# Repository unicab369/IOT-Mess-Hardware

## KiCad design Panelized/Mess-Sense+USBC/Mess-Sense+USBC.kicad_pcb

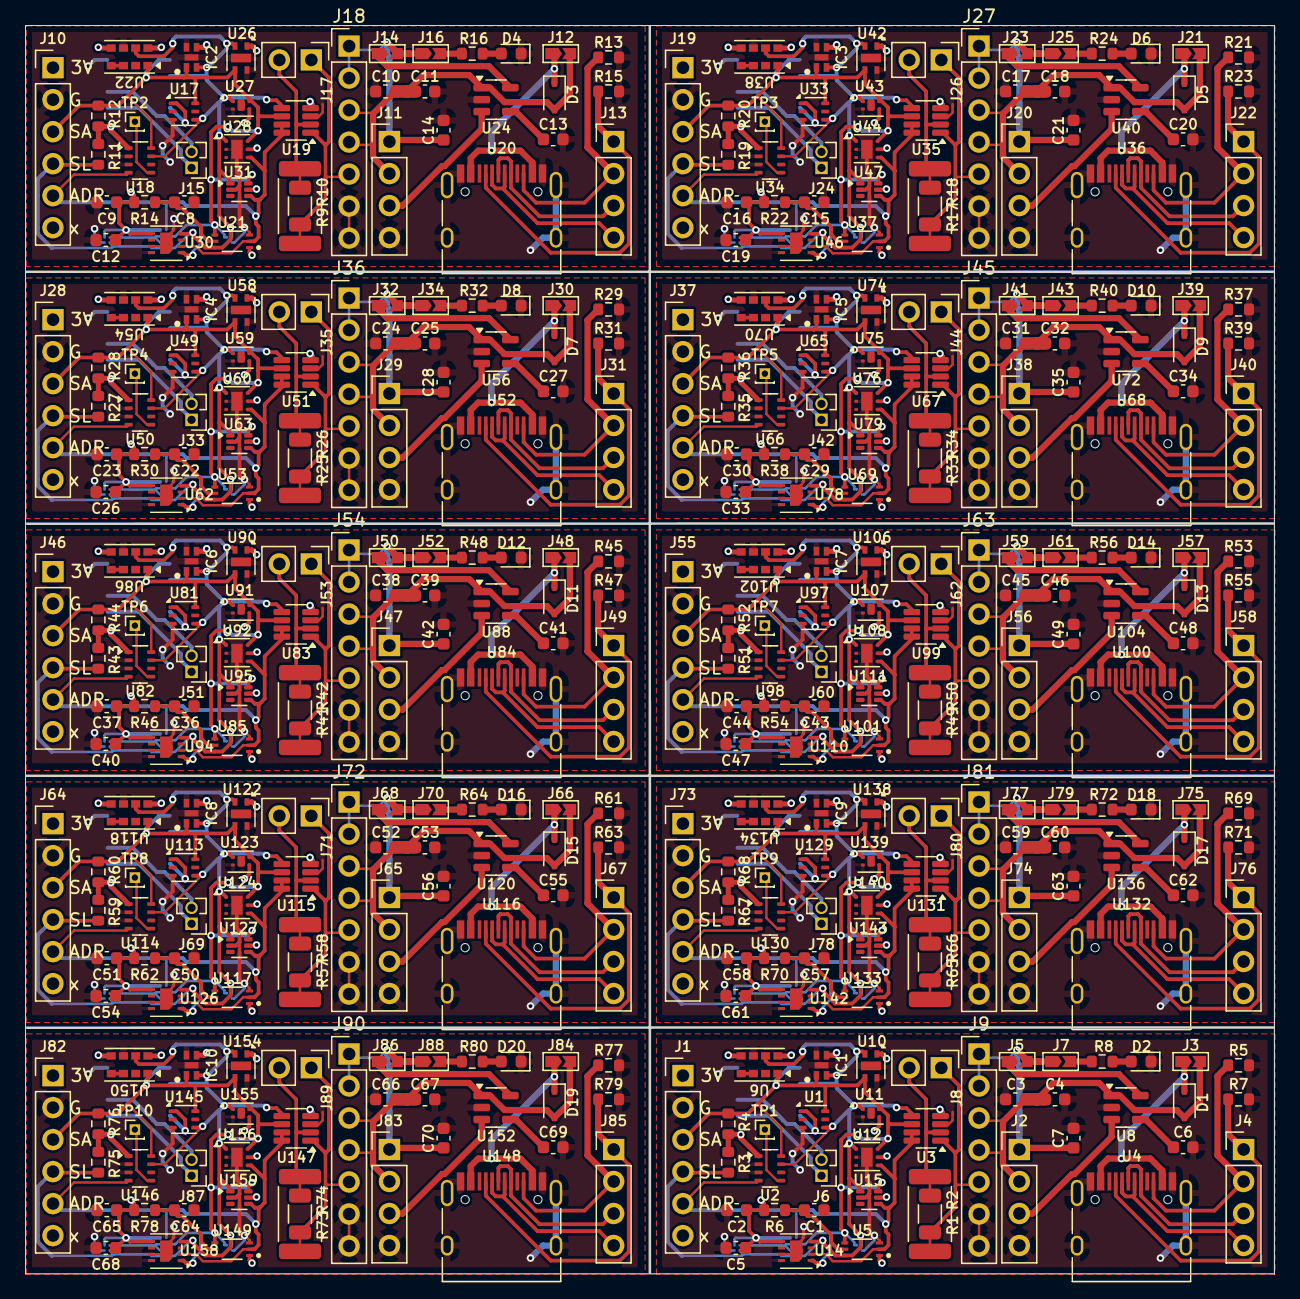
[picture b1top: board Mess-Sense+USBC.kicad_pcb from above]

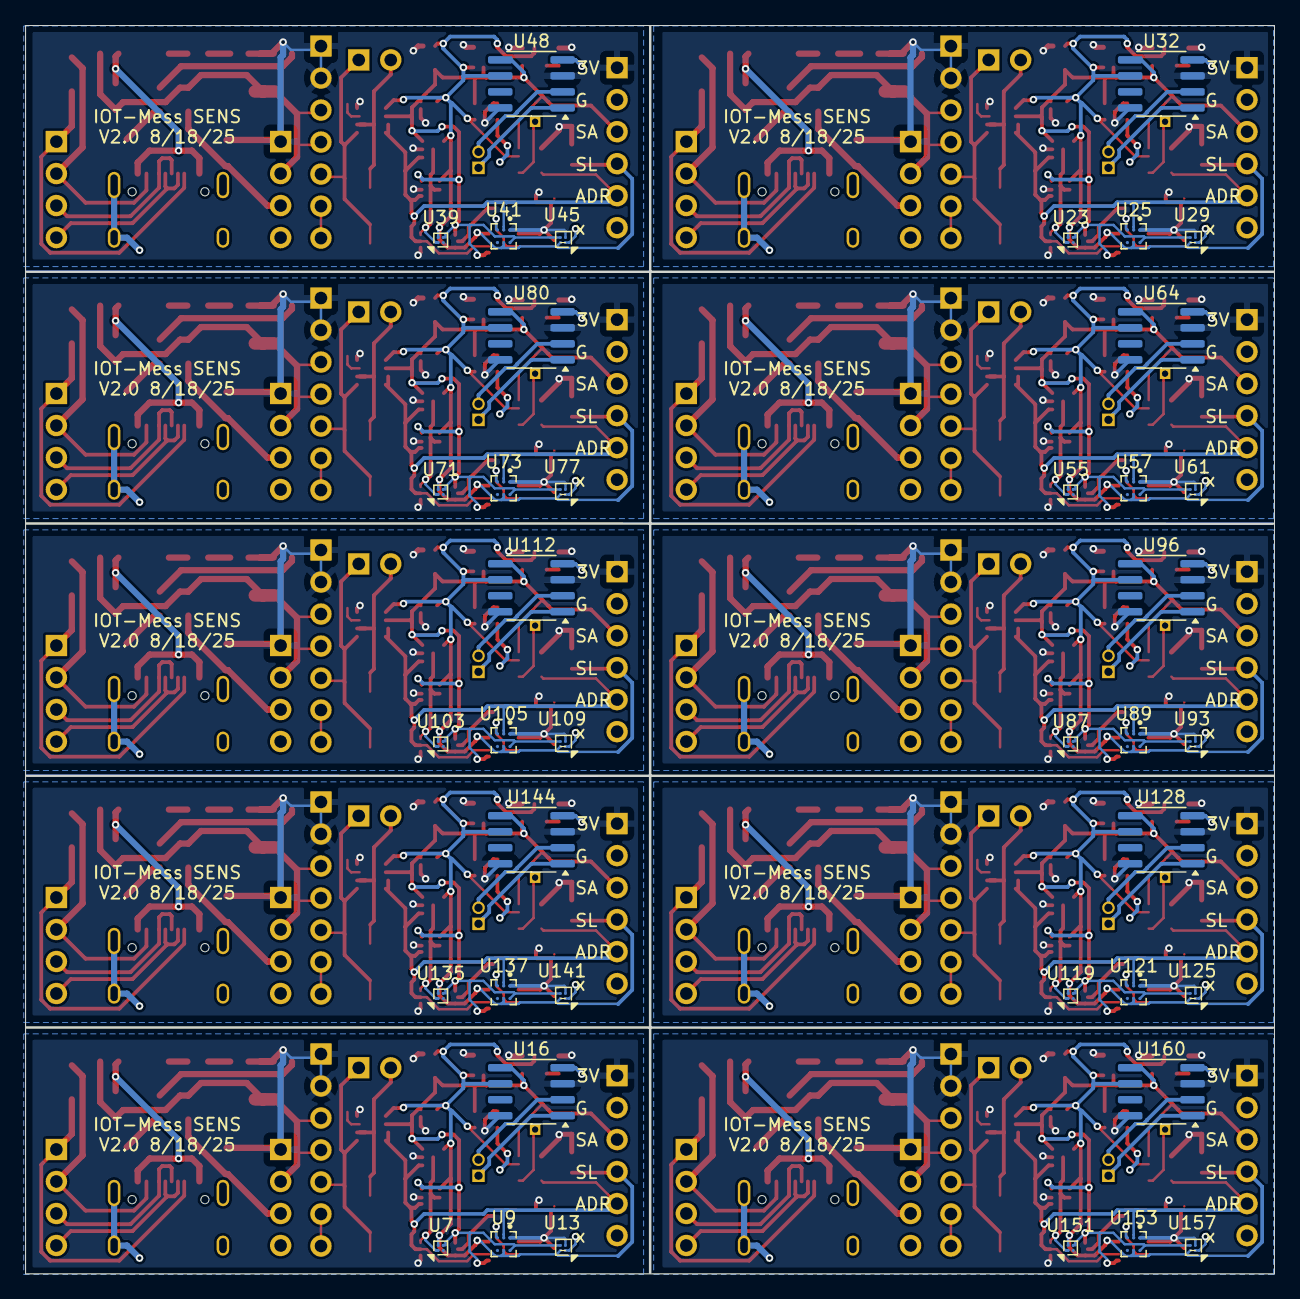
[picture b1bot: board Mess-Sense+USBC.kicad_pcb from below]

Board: 2 copper layers, 99.1 x 99.1 mm, 440 parts (40 on the bottom side), 23 nets.

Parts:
C1, C8, C15, C22, C29, C36, C43, C50, C57, C64: 0.1uF; C_0603_1608Metric
C2, C9, C16, C23, C30, C37, C44, C51, C58, C65: 1uF; C_0603_1608Metric
C3, C10, C17, C24, C31, C38, C45, C52, C59, C66: 10u; C_0603_1608Metric
C4, C7, C11, C14, C18, C21, C25, C28, C32, C35, C39, C42, C46, C49, C53, C56, C60, C63, C67, C70: 1u; C_0603_1608Metric
C5, C12, C19, C26, C33, C40, C47, C54, C61, C68: 2.2uF; C_0603_1608Metric
C6, C13, C20, C27, C34, C41, C48, C55, C62, C69: 22nF; C_0603_1608Metric
D1, D3, D5, D7, D9, D11, D13, D15, D17, D19: 1N5819WS; D_SOD-323
D2, D4, D6, D8, D10, D12, D14, D16, D18, D20: LED; LED_0603_1608Metric
IC1, IC2, IC3, IC4, IC5, IC6, IC7, IC8, IC9, IC10: SHT40I-AD1F-R2; SON80P150X150X59-5N
J1, J10, J19, J28, J37, J46, J55, J64, J73, J82: Conn_01x06_Pin; PinHeader_1x06_P2.54mm_Vertical
J2, J4, J11, J13, J20, J22, J29, J31, J38, J40, J47, J49, J56, J58, J65, J67, J74, J76, J83, J85: Conn_01x04_Pin; PinHeader_1x04_P2.54mm_Vertical
J3, J5, J7, J12, J14, J16, J21, J23, J25, J30, J32, J34, J39, J41, J43, J48, J50, J52, J57, J59, J61, J66, J68, J70, J75, J77, J79, J84, J86, J88: Jumper_2; Jumpper-triangle
J6, J15, J24, J33, J42, J51, J60, J69, J78, J87: Conn_01x02_Pin; PinHeader_1x02_P1.27mm_Vertical
J8, J17, J26, J35, J44, J53, J62, J71, J80, J89: Conn_01x02_Pin; PinHeader_1x02_P2.54mm_Vertical
J9, J18, J27, J36, J45, J54, J63, J72, J81, J90: Conn_01x07_Pin; PinHeader_1x07_P2.54mm_Vertical
R1, R9, R17, R25, R33, R41, R49, R57, R65, R73: 0.1; R_2512_6332Metric
R2, R10, R18, R26, R34, R42, R50, R58, R66, R74: 0.1; R_1206_3216Metric
R3, R4, R11, R12, R19, R20, R27, R28, R35, R36, R43, R44, R51, R52, R59, R60, R67, R68, R75, R76: 10K; R_0603_1608Metric
R5, R7, R13, R15, R21, R23, R29, R31, R37, R39, R45, R47, R53, R55, R61, R63, R69, R71, R77, R79: 5.1K; R_0603_1608Metric
R6, R14, R22, R30, R38, R46, R54, R62, R70, R78: 5K; R_0603_1608Metric
R8, R16, R24, R32, R40, R48, R56, R64, R72, R80: R; R_0603_1608Metric
TP1, TP2, TP3, TP4, TP5, TP6, TP7, TP8, TP9, TP10: TestPoint; PinHeader_1x01_P1.00mm_Vertical
U1, U17, U33, U49, U65, U81, U97, U113, U129, U145: LTR-303/308; Lite-On_LTR-303ALS-01
U2, U18, U34, U50, U66, U82, U98, U114, U130, U146: LTR-507ALS
U3, U19, U35, U51, U67, U83, U99, U115, U131, U147: INA219AxDCN; SOT-23-8
U4, U20, U36, U52, U68, U84, U100, U116, U132, U148: USB_C_Receptacle_USB2.0_16P; USB_C_Receptacle_HRO_TYPE-C-31-M-12
U5, U21, U37, U53, U69, U85, U101, U117, U133, U149: BH1750FVI-TR; XDCR_BH1750FVI-TR
U6, U22, U38, U54, U70, U86, U102, U118, U134, U150: APDS-9960; Avago_APDS-9960
U7, U23, U39, U55, U71, U87, U103, U119, U135, U151: MMC5633NJL/WLP-4; WLP-4_0.86x0.86mm_P0.4mm
U8, U24, U40, U56, U72, U88, U104, U120, U136, U152: ME6211C33M5; SOT-23-5
U9, U25, U41, U57, U73, U89, U105, U121, U137, U153: HDC2010/DSBGA-6; BGA6C100X50P2X3_HDC2010YPAR
U10, U26, U42, U58, U74, U90, U106, U122, U138, U154: ENS210; AMS_QFN-4-1EP_2x2mm_P0.95mm_EP0.7x1.6mm
U11, U27, U43, U59, U75, U91, U107, U123, U139, U155: MTS4 0.1C DFN-4L; DFN-4L
U12, U28, U44, U60, U76, U92, U108, U124, U140, U156: T117W 0.1C DFN-6L; DFN-6L
U13, U29, U45, U61, U77, U93, U109, U125, U141, U157: QMC6309/WLCSP-4; WLCSP-4_0.8x0.8mm_Layout2x2_P0.4mm
U14, U30, U46, U62, U78, U94, U110, U126, U142, U158: SHT31-DIS; Sensirion_DFN-8-1EP_2.5x2.5mm_P0.5mm_EP1.1x1.7mm
U15, U31, U47, U63, U79, U95, U111, U127, U143, U159: TMP102xxDRL 0.5C SOT-563; SOT-563
U16, U32, U48, U64, U80, U96, U112, U128, U144, U160: DS1307Z+; SOIC-8_3.9x4.9mm_P1.27mm

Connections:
5V: C3.1, C4.1, C10.1, C11.1, C17.1, C18.1, C24.1, C25.1, C31.1, C32.1, C38.1, C39.1, C45.1, C46.1, C52.1, C53.1, C59.1, C60.1, C66.1, C67.1, D1.2 (A), D3.2 (A), D5.2 (A), D7.2 (A), D9.2 (A), D11.2 (A), D13.2 (A), D15.2 (A), D17.2 (A), D19.2 (A), J2.2, J3.2 (B), J9.3, J9.4, J11.2, J12.2 (B), J18.3, J18.4, J20.2, J21.2 (B), J27.3, J27.4, J29.2, J30.2 (B), J36.3, J36.4, J38.2, J39.2 (B), J45.3, J45.4, J47.2, J48.2 (B), J54.3, J54.4, J56.2, J57.2 (B), J63.3, J63.4, J65.2, J66.2 (B), J72.3, J72.4, J74.2, J75.2 (B), J81.3, J81.4, J83.2, J84.2 (B), J90.3, J90.4, U8.1 (V_{IN}), U24.1 (V_{IN}), U40.1 (V_{IN}), U56.1 (V_{IN}), U72.1 (V_{IN}), U88.1 (V_{IN}), U104.1 (V_{IN}), U120.1 (V_{IN}), U136.1 (V_{IN}), U152.1 (V_{IN})
+3.3V: C2.1, C5.1, C7.1, C9.1, C12.1, C14.1, C16.1, C19.1, C21.1, C23.1, C26.1, C28.1, C30.1, C33.1, C35.1, C37.1, C40.1, C42.1, C44.1, C47.1, C49.1, C51.1, C54.1, C56.1, C58.1, C61.1, C63.1, C65.1, C68.1, C70.1, IC1.3 (VDD), IC2.3 (VDD), IC3.3 (VDD), IC4.3 (VDD), IC5.3 (VDD), IC6.3 (VDD), IC7.3 (VDD), IC8.3 (VDD), IC9.3 (VDD), IC10.3 (VDD), J1.1, J2.1, J5.2 (B), J7.1 (A), J9.1, J9.2, J10.1, J11.1, J14.2 (B), J16.1 (A), J18.1, J18.2, J19.1, J20.1, J23.2 (B), J25.1 (A), J27.1, J27.2, J28.1, J29.1, J32.2 (B), J34.1 (A), J36.1, J36.2, J37.1, J38.1, J41.2 (B), J43.1 (A), J45.1, J45.2, J46.1, J47.1, J50.2 (B), J52.1 (A), J54.1, J54.2, J55.1, J56.1, J59.2 (B), J61.1 (A), J63.1, J63.2, J64.1, J65.1, J68.2 (B), J70.1 (A), J72.1, J72.2, J73.1, J74.1, J77.2 (B), J79.1 (A), J81.1, J81.2, J82.1, J83.1, J86.2 (B), J88.1 (A), J90.1, J90.2, R3.2, R4.1, R6.1, R11.2, R12.1, R14.1, R19.2, R20.1, R22.1, R27.2, R28.1, R30.1, R35.2, R36.1, R38.1, R43.2, R44.1, R46.1, R51.2, R52.1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
ADDR: J1.5, J10.5, J19.5, J28.5, J37.5, J46.5, J55.5, J64.5, J73.5, J82.5, U2.4 (ADDR), U3.7 (A0), U3.8 (A1), U5.2 (ADDR), U9.B1 (ADDR), U12.4 (ADDR), U14.2 (ADDR), U15.4 (ADD0), U18.4 (ADDR), U19.7 (A0), U19.8 (A1), U21.2 (ADDR), U25.B1 (ADDR), U28.4 (ADDR), U30.2 (ADDR), U31.4 (ADD0), U34.4 (ADDR), U35.7 (A0), U35.8 (A1), U37.2 (ADDR), U41.B1 (ADDR), U44.4 (ADDR), U46.2 (ADDR), U47.4 (ADD0), U50.4 (ADDR), U51.7 (A0), U51.8 (A1), U53.2 (ADDR), U57.B1 (ADDR), U60.4 (ADDR), U62.2 (ADDR), U63.4 (ADD0), U66.4 (ADDR), U67.7 (A0), U67.8 (A1), U69.2 (ADDR), U73.B1 (ADDR), U76.4 (ADDR), U78.2 (ADDR), U79.4 (ADD0), U82.4 (ADDR), U83.7 (A0), U83.8 (A1), U85.2 (ADDR), U89.B1 (ADDR), U92.4 (ADDR), U94.2 (ADDR), U95.4 (ADD0), U98.4 (ADDR), U99.7 (A0), U99.8 (A1), U101.2 (ADDR), U105.B1 (ADDR), U108.4 (ADDR), U110.2 (ADDR), U111.4 (ADD0), U114.4 (ADDR), U115.7 (A0), U115.8 (A1), U117.2 (ADDR), U121.B1 (ADDR), U124.4 (ADDR), U126.2 (ADDR), U127.4 (ADD0), U130.4 (ADDR), U131.7 (A0), U131.8 (A1), U133.2 (ADDR), U137.B1 (ADDR), U140.4 (ADDR), U142.2 (ADDR), U143.4 (ADD0), U146.4 (ADDR), U147.7 (A0), U147.8 (A1), U149.2 (ADDR), U153.B1 (ADDR), U156.4 (ADDR), U158.2 (ADDR), U159.4 (ADD0)
CC1: J4.1, J13.1, J22.1, J31.1, J40.1, J49.1, J58.1, J67.1, J76.1, J85.1, R7.1, R15.1, R23.1, R31.1, R39.1, R47.1, R55.1, R63.1, R71.1, R79.1, U4.A5 (CC1), U20.A5 (CC1), U36.A5 (CC1), U52.A5 (CC1), U68.A5 (CC1), U84.A5 (CC1), U100.A5 (CC1), U116.A5 (CC1), U132.A5 (CC1), U148.A5 (CC1)
CC2: J4.2, J13.2, J22.2, J31.2, J40.2, J49.2, J58.2, J67.2, J76.2, J85.2, R5.1, R13.1, R21.1, R29.1, R37.1, R45.1, R53.1, R61.1, R69.1, R77.1, U4.B5 (CC2), U20.B5 (CC2), U36.B5 (CC2), U52.B5 (CC2), U68.B5 (CC2), U84.B5 (CC2), U100.B5 (CC2), U116.B5 (CC2), U132.B5 (CC2), U148.B5 (CC2)
CE: J2.3, J11.3, J20.3, J29.3, J38.3, J47.3, J56.3, J65.3, J74.3, J83.3, U8.3 (CE), U24.3 (CE), U40.3 (CE), U56.3 (CE), U72.3 (CE), U88.3 (CE), U104.3 (CE), U120.3 (CE), U136.3 (CE), U152.3 (CE)
D+: J4.3, J13.3, J22.3, J31.3, J40.3, J49.3, J58.3, J67.3, J76.3, J85.3, U4.A6 (D+), U4.B6 (D+), U20.A6 (D+), U20.B6 (D+), U36.A6 (D+), U36.B6 (D+), U52.A6 (D+), U52.B6 (D+), U68.A6 (D+), U68.B6 (D+), U84.A6 (D+), U84.B6 (D+), U100.A6 (D+), U100.B6 (D+), U116.A6 (D+), U116.B6 (D+), U132.A6 (D+), U132.B6 (D+), U148.A6 (D+), U148.B6 (D+)
D-: J4.4, J13.4, J22.4, J31.4, J40.4, J49.4, J58.4, J67.4, J76.4, J85.4, U4.A7 (D-), U4.B7 (D-), U20.A7 (D-), U20.B7 (D-), U36.A7 (D-), U36.B7 (D-), U52.A7 (D-), U52.B7 (D-), U68.A7 (D-), U68.B7 (D-), U84.A7 (D-), U84.B7 (D-), U100.A7 (D-), U100.B7 (D-), U116.A7 (D-), U116.B7 (D-), U132.A7 (D-), U132.B7 (D-), U148.A7 (D-), U148.B7 (D-)
GND: C1.2, C2.2, C3.2, C4.2, C5.2, C6.2, C7.2, C8.2, C9.2, C10.2, C11.2, C12.2, C13.2, C14.2, C15.2, C16.2, C17.2, C18.2, C19.2, C20.2, C21.2, C22.2, C23.2, C24.2, C25.2, C26.2, C27.2, C28.2, C29.2, C30.2, C31.2, C32.2, C33.2, C34.2, C35.2, C36.2, C37.2, C38.2, C39.2, C40.2, C41.2, C42.2, C43.2, C44.2, C45.2, C46.2, C47.2, C48.2, C49.2, C50.2, C51.2, C52.2, C53.2, C54.2, C55.2, C56.2, C57.2, C58.2, C59.2, C60.2, C61.2, C62.2, C63.2, C64.2, C65.2, C66.2, C67.2, C68.2, C69.2, C70.2, D2.1 (K), D4.1 (K), D6.1 (K), D8.1 (K), D10.1 (K), D12.1 (K), D14.1 (K), D16.1 (K), D18.1 (K), D20.1 (K), IC1.4 (VSS), IC1.5 (EP), IC2.4 (VSS), IC2.5 (EP), IC3.4 (VSS), IC3.5 (EP), IC4.4 (VSS), IC4.5 (EP), IC5.4 (VSS), IC5.5 (EP), IC6.4 (VSS), IC6.5 (EP), IC7.4 (VSS), IC7.5 (EP), IC8.4 (VSS), IC8.5 (EP), IC9.4 (VSS), IC9.5 (EP), IC10.4 (VSS), IC10.5 (EP), J1.2, J2.4, J9.6, J9.7, J10.2, J11.4, J18.6, J18.7, J19.2, J20.4, J27.6, J27.7, J28.2, J29.4, J36.6, J36.7, J37.2, J38.4, J45.6, J45.7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
unnamed: D1.1 (K), D3.1 (K), D5.1 (K), D7.1 (K), D9.1 (K), D11.1 (K), D13.1 (K), D15.1 (K), D17.1 (K), D19.1 (K), J3.1 (A), J12.1 (A), J21.1 (A), J30.1 (A), J39.1 (A), J48.1 (A), J57.1 (A), J66.1 (A), J75.1 (A), J84.1 (A), U4.A4 (VBUS), U4.A9 (VBUS), U4.B4 (VBUS), U4.B9 (VBUS), U20.A4 (VBUS), U20.A9 (VBUS), U20.B4 (VBUS), U20.B9 (VBUS), U36.A4 (VBUS), U36.A9 (VBUS), U36.B4 (VBUS), U36.B9 (VBUS), U52.A4 (VBUS), U52.A9 (VBUS), U52.B4 (VBUS), U52.B9 (VBUS), U68.A4 (VBUS), U68.A9 (VBUS), U68.B4 (VBUS), U68.B9 (VBUS), U84.A4 (VBUS), U84.A9 (VBUS), U84.B4 (VBUS), U84.B9 (VBUS), U100.A4 (VBUS), U100.A9 (VBUS), U100.B4 (VBUS), U100.B9 (VBUS), U116.A4 (VBUS), U116.A9 (VBUS), U116.B4 (VBUS), U116.B9 (VBUS), U132.A4 (VBUS), U132.A9 (VBUS), U132.B4 (VBUS), U132.B9 (VBUS), U148.A4 (VBUS), U148.A9 (VBUS), U148.B4 (VBUS), U148.B9 (VBUS)
unnamed: D2.2 (A), D4.2 (A), D6.2 (A), D8.2 (A), D10.2 (A), D12.2 (A), D14.2 (A), D16.2 (A), D18.2 (A), D20.2 (A), R8.1, R16.1, R24.1, R32.1, R40.1, R48.1, R56.1, R64.1, R72.1, R80.1
unnamed: J5.1 (A), J14.1 (A), J23.1 (A), J32.1 (A), J41.1 (A), J50.1 (A), J59.1 (A), J68.1 (A), J77.1 (A), J86.1 (A), U8.5 (V_{OUT}), U24.5 (V_{OUT}), U40.5 (V_{OUT}), U56.5 (V_{OUT}), U72.5 (V_{OUT}), U88.5 (V_{OUT}), U104.5 (V_{OUT}), U120.5 (V_{OUT}), U136.5 (V_{OUT}), U152.5 (V_{OUT})
unnamed: J6.1, J15.1, J24.1, J33.1, J42.1, J51.1, J60.1, J69.1, J78.1, J87.1, U16.1 (X1), U32.1 (X1), U48.1 (X1), U64.1 (X1), U80.1 (X1), U96.1 (X1), U112.1 (X1), U128.1 (X1), U144.1 (X1), U160.1 (X1)
unnamed: J6.2, J15.2, J24.2, J33.2, J42.2, J51.2, J60.2, J69.2, J78.2, J87.2, U16.2 (X2), U32.2 (X2), U48.2 (X2), U64.2 (X2), U80.2 (X2), U96.2 (X2), U112.2 (X2), U128.2 (X2), U144.2 (X2), U160.2 (X2)
unnamed: J7.2 (B), J16.2 (B), J25.2 (B), J34.2 (B), J43.2 (B), J52.2 (B), J61.2 (B), J70.2 (B), J79.2 (B), J88.2 (B), R8.2, R16.2, R24.2, R32.2, R40.2, R48.2, R56.2, R64.2, R72.2, R80.2
unnamed: J8.1, J9.5, J17.1, J18.5, J26.1, J27.5, J35.1, J36.5, J44.1, J45.5, J53.1, J54.5, J62.1, J63.5, J71.1, J72.5, J80.1, J81.5, J89.1, J90.5, R1.1, R2.1, R9.1, R10.1, R17.1, R18.1, R25.1, R26.1, R33.1, R34.1, R41.1, R42.1, R49.1, R50.1, R57.1, R58.1, R65.1, R66.1, R73.1, R74.1, U3.1 (IN+), U19.1 (IN+), U35.1 (IN+), U51.1 (IN+), U67.1 (IN+), U83.1 (IN+), U99.1 (IN+), U115.1 (IN+), U131.1 (IN+), U147.1 (IN+)
unnamed: J8.2, J17.2, J26.2, J35.2, J44.2, J53.2, J62.2, J71.2, J80.2, J89.2, R1.2, R2.2, R9.2, R10.2, R17.2, R18.2, R25.2, R26.2, R33.2, R34.2, R41.2, R42.2, R49.2, R50.2, R57.2, R58.2, R65.2, R66.2, R73.2, R74.2, U3.2 (IN-), U19.2 (IN-), U35.2 (IN-), U51.2 (IN-), U67.2 (IN-), U83.2 (IN-), U99.2 (IN-), U115.2 (IN-), U131.2 (IN-), U147.2 (IN-)
unnamed: TP1.1, TP2.1, TP3.1, TP4.1, TP5.1, TP6.1, TP7.1, TP8.1, TP9.1, TP10.1, U2.5 (VLED), U18.5 (VLED), U34.5 (VLED), U50.5 (VLED), U66.5 (VLED), U82.5 (VLED), U98.5 (VLED), U114.5 (VLED), U130.5 (VLED), U146.5 (VLED)
unnamed: C1.1, C8.1, C15.1, C22.1, C29.1, C36.1, C43.1, C50.1, C57.1, C64.1, R6.2, R14.2, R22.2, R30.2, R38.2, R46.2, R54.2, R62.2, R70.2, R78.2, U5.5 (DVI), U21.5 (DVI), U37.5 (DVI), U53.5 (DVI), U69.5 (DVI), U85.5 (DVI), U101.5 (DVI), U117.5 (DVI), U133.5 (DVI), U149.5 (DVI)
unnamed: U6.3 (LDR), U6.4 (LED_K), U22.3 (LDR), U22.4 (LED_K), U38.3 (LDR), U38.4 (LED_K), U54.3 (LDR), U54.4 (LED_K), U70.3 (LDR), U70.4 (LED_K), U86.3 (LDR), U86.4 (LED_K), U102.3 (LDR), U102.4 (LED_K), U118.3 (LDR), U118.4 (LED_K), U134.3 (LDR), U134.4 (LED_K), U150.3 (LDR), U150.4 (LED_K)
unnamed: C6.1, C13.1, C20.1, C27.1, C34.1, C41.1, C48.1, C55.1, C62.1, C69.1, U8.4 (NC), U24.4 (NC), U40.4 (NC), U56.4 (NC), U72.4 (NC), U88.4 (NC), U104.4 (NC), U120.4 (NC), U136.4 (NC), U152.4 (NC)
SCL_0: IC1.2 (SCL), IC2.2 (SCL), IC3.2 (SCL), IC4.2 (SCL), IC5.2 (SCL), IC6.2 (SCL), IC7.2 (SCL), IC8.2 (SCL), IC9.2 (SCL), IC10.2 (SCL), J1.4, J10.4, J19.4, J28.4, J37.4, J46.4, J55.4, J64.4, J73.4, J82.4, R3.1, R11.1, R19.1, R27.1, R35.1, R43.1, R51.1, R59.1, R67.1, R75.1, U1.4 (SCL), U2.7 (SCL), U3.5 (SCL), U5.6 (SCL), U6.7 (SCL), U7.A2 (SCL), U9.B2 (SCL), U10.2 (SCL), U11.1 (SCL), U12.1 (SCL), U13.A2 (SCL), U14.4 (SCL), U15.1 (SCL), U16.6 (SCL), U17.4 (SCL), U18.7 (SCL), U19.5 (SCL), U21.6 (SCL), U22.7 (SCL), U23.A2 (SCL), U25.B2 (SCL), U26.2 (SCL), U27.1 (SCL), U28.1 (SCL), U29.A2 (SCL), U30.4 (SCL), U31.1 (SCL), U32.6 (SCL), U33.4 (SCL), U34.7 (SCL), U35.5 (SCL), U37.6 (SCL), U38.7 (SCL), U39.A2 (SCL), U41.B2 (SCL), U42.2 (SCL), U43.1 (SCL), U44.1 (SCL), U45.A2 (SCL), U46.4 (SCL), U47.1 (SCL), U48.6 (SCL), U49.4 (SCL), U50.7 (SCL), U51.5 (SCL), U53.6 (SCL), U54.7 (SCL), U55.A2 (SCL), U57.B2 (SCL), U58.2 (SCL), U59.1 (SCL), U60.1 (SCL), U61.A2 (SCL), U62.4 (SCL), U63.1 (SCL), U64.6 (SCL), U65.4 (SCL), U66.7 (SCL), U67.5 (SCL), U69.6 (SCL), U70.7 (SCL), U71.A2 (SCL), U73.B2 (SCL), U74.2 (SCL), U75.1 (SCL), U76.1 (SCL), U77.A2 (SCL), U78.4 (SCL), U79.1 (SCL), U80.6 (SCL), U81.4 (SCL), U82.7 (SCL), U83.5 (SCL), U85.6 (SCL), U86.7 (SCL), U87.A2 (SCL), U89.B2 (SCL), U90.2 (SCL), U91.1 (SCL), U92.1 (SCL), U93.A2 (SCL), U94.4 (SCL), U95.1 (SCL), U96.6 (SCL), U97.4 (SCL), U98.7 (SCL), U99.5 (SCL), U101.6 (SCL), U102.7 (SCL), U103.A2 (SCL)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
SDA_0: IC1.1 (SDA), IC2.1 (SDA), IC3.1 (SDA), IC4.1 (SDA), IC5.1 (SDA), IC6.1 (SDA), IC7.1 (SDA), IC8.1 (SDA), IC9.1 (SDA), IC10.1 (SDA), J1.3, J10.3, J19.3, J28.3, J37.3, J46.3, J55.3, J64.3, J73.3, J82.3, R4.2, R12.2, R20.2, R28.2, R36.2, R44.2, R52.2, R60.2, R68.2, R76.2, U1.6 (SDA), U2.8 (SDA), U3.6 (SDA), U5.4 (SDA), U6.1 (SDA), U7.B2 (SDA), U9.A2 (SDA), U10.3 (SDA), U11.4 (SDA), U12.6 (SDA), U13.B2 (SDA), U14.1 (SDA), U15.6 (SDA), U16.5 (SDA), U17.6 (SDA), U18.8 (SDA), U19.6 (SDA), U21.4 (SDA), U22.1 (SDA), U23.B2 (SDA), U25.A2 (SDA), U26.3 (SDA), U27.4 (SDA), U28.6 (SDA), U29.B2 (SDA), U30.1 (SDA), U31.6 (SDA), U32.5 (SDA), U33.6 (SDA), U34.8 (SDA), U35.6 (SDA), U37.4 (SDA), U38.1 (SDA), U39.B2 (SDA), U41.A2 (SDA), U42.3 (SDA), U43.4 (SDA), U44.6 (SDA), U45.B2 (SDA), U46.1 (SDA), U47.6 (SDA), U48.5 (SDA), U49.6 (SDA), U50.8 (SDA), U51.6 (SDA), U53.4 (SDA), U54.1 (SDA), U55.B2 (SDA), U57.A2 (SDA), U58.3 (SDA), U59.4 (SDA), U60.6 (SDA), U61.B2 (SDA), U62.1 (SDA), U63.6 (SDA), U64.5 (SDA), U65.6 (SDA), U66.8 (SDA), U67.6 (SDA), U69.4 (SDA), U70.1 (SDA), U71.B2 (SDA), U73.A2 (SDA), U74.3 (SDA), U75.4 (SDA), U76.6 (SDA), U77.B2 (SDA), U78.1 (SDA), U79.6 (SDA), U80.5 (SDA), U81.6 (SDA), U82.8 (SDA), U83.6 (SDA), U85.4 (SDA), U86.1 (SDA), U87.B2 (SDA), U89.A2 (SDA), U90.3 (SDA), U91.4 (SDA), U92.6 (SDA), U93.B2 (SDA), U94.1 (SDA), U95.6 (SDA), U96.5 (SDA), U97.6 (SDA), U98.8 (SDA), U99.6 (SDA), U101.4 (SDA), U102.1 (SDA), U103.B2 (SDA)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

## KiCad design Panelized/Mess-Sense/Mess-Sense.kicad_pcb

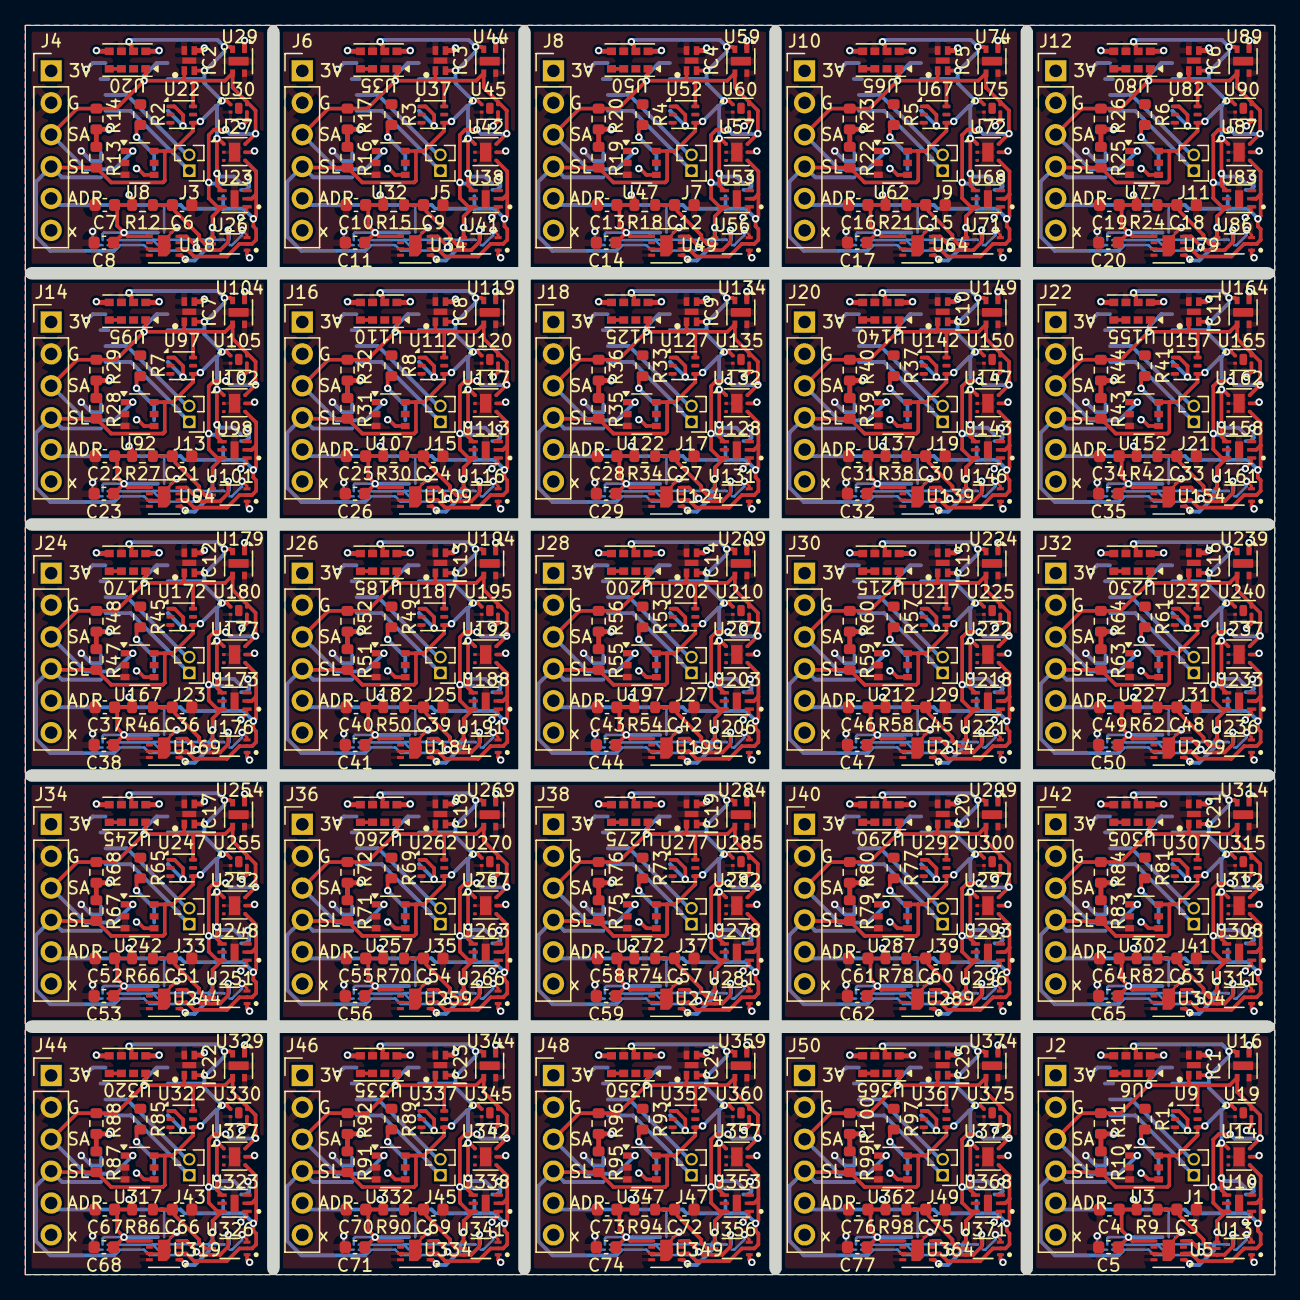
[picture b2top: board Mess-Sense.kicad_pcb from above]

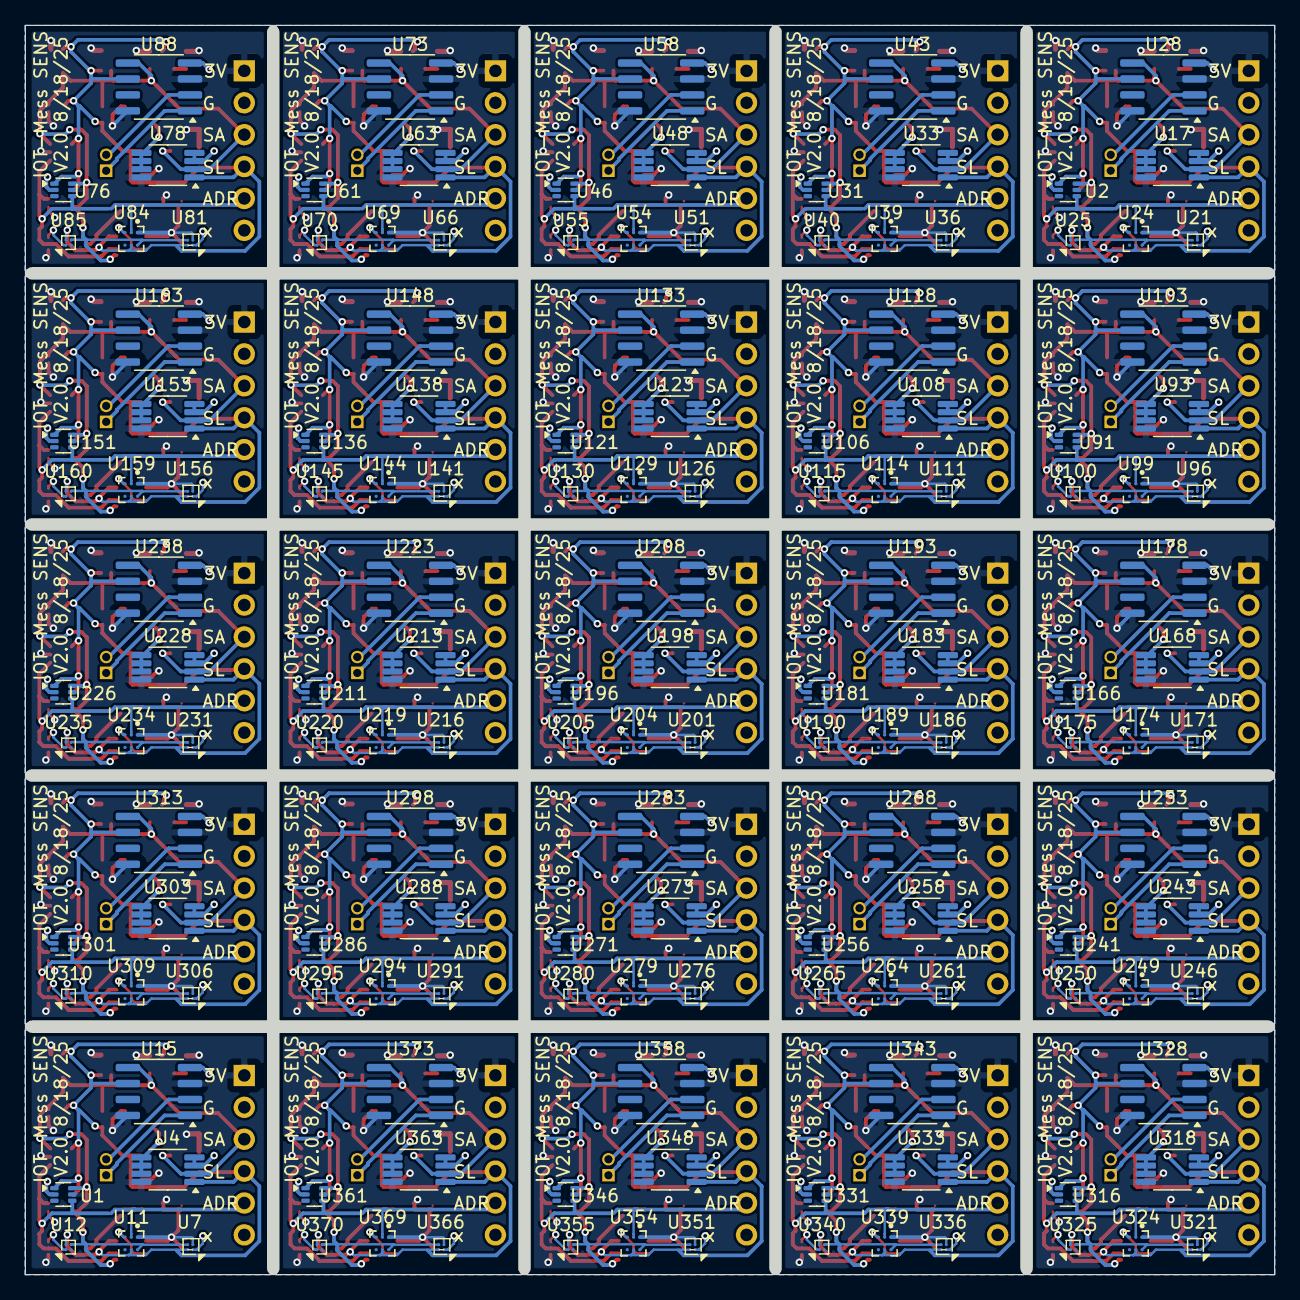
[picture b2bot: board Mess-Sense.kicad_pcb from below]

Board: 2 copper layers, 99.5 x 99.5 mm, 625 parts (150 on the bottom side), 10 nets.

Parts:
C3, C6, C9, C12, C15, C18, C21, C24, C27, C30, C33, C36, C39, C42, C45, C48, C51, C54, C57, C60, C63, C66, C69, C72, C75: 0.1uF; C_0603_1608Metric
C4, C7, C10, C13, C16, C19, C22, C25, C28, C31, C34, C37, C40, C43, C46, C49, C52, C55, C58, C61, C64, C67, C70, C73, C76: 1uF; C_0603_1608Metric
C5, C8, C11, C14, C17, C20, C23, C26, C29, C32, C35, C38, C41, C44, C47, C50, C53, C56, C59, C62, C65, C68, C71, C74, C77: 2.2uF; C_0603_1608Metric
IC1, IC2, IC3, IC4, IC5, IC6, IC7, IC8, IC9, IC10, IC11, IC12, IC13, IC14, IC15, IC16, IC17, IC18, IC19, IC20, IC21, IC22, IC23, IC24, IC25: SHT40I-AD1F-R2; SON80P150X150X59-5N
J1, J3, J5, J7, J9, J11, J13, J15, J17, J19, J21, J23, J25, J27, J29, J31, J33, J35, J37, J39, J41, J43, J45, J47, J49: Conn_01x02_Pin; PinHeader_1x02_P1.27mm_Vertical
J2, J4, J6, J8, J10, J12, J14, J16, J18, J20, J22, J24, J26, J28, J30, J32, J34, J36, J38, J40, J42, J44, J46, J48, J50: Conn_01x06_Pin; PinHeader_1x06_P2.54mm_Vertical
R1, R2, R3, R4, R5, R6, R7, R8, R10, R11, R13, R14, R16, R17, R19, R20, R22, R23, R25, R26, R28, R29, R31, R32, R33, R35, R36, R37, R39, R40, R41, R43, R44, R45, R47, R48, R49, R51, R52, R53, R55, R56, R57, R59, R60, R61, R63, R64, R65, R67, R68, R69, R71, R72, R73, R75, R76, R77, R79, R80, R81, R83, R84, R85, R87, R88, R89, R91, R92, R93, R95, R96, R97, R99, R100: 10K; R_0603_1608Metric
R9, R12, R15, R18, R21, R24, R27, R30, R34, R38, R42, R46, R50, R54, R58, R62, R66, R70, R74, R78, R82, R86, R90, R94, R98: 5K; R_0603_1608Metric
U1, U2, U31, U46, U61, U76, U91, U106, U121, U136, U151, U166, U181, U196, U211, U226, U241, U256, U271, U286, U301, U316, U331, U346, U361: TMP102xxDRL; SOT-563
U3, U8, U32, U47, U62, U77, U92, U107, U122, U137, U152, U167, U182, U197, U212, U227, U242, U257, U272, U287, U302, U317, U332, U347, U362: TLV493D; TSOP-6_1.65x3.05mm_P0.95mm
U4, U17, U33, U48, U63, U78, U93, U108, U123, U138, U153, U168, U183, U198, U213, U228, U243, U258, U273, U288, U303, U318, U333, U348, U363: TMP1075DGK; VSSOP-8_3x3mm_P0.65mm
U5, U18, U34, U49, U64, U79, U94, U109, U124, U139, U154, U169, U184, U199, U214, U229, U244, U259, U274, U289, U304, U319, U334, U349, U364: SHT31-DIS; Sensirion_DFN-8-1EP_2.5x2.5mm_P0.5mm_EP1.1x1.7mm
U6, U20, U35, U50, U65, U80, U95, U110, U125, U140, U155, U170, U185, U200, U215, U230, U245, U260, U275, U290, U305, U320, U335, U350, U365: APDS-9960; Avago_APDS-9960
U7, U21, U36, U51, U66, U81, U96, U111, U126, U141, U156, U171, U186, U201, U216, U231, U246, U261, U276, U291, U306, U321, U336, U351, U366: QMC6309/WLCSP-4; WLCSP-4_0.8x0.8mm_Layout2x2_P0.4mm
U9, U22, U37, U52, U67, U82, U97, U112, U127, U142, U157, U172, U187, U202, U217, U232, U247, U262, U277, U292, U307, U322, U337, U352, U367: LTR-303ALS-01; Lite-On_LTR-303ALS-01
U10, U23, U38, U53, U68, U83, U98, U113, U128, U143, U158, U173, U188, U203, U218, U233, U248, U263, U278, U293, U308, U323, U338, U353, U368: OPT3001DNPR; SON65P200X200X65-7N
U11, U24, U39, U54, U69, U84, U99, U114, U129, U144, U159, U174, U189, U204, U219, U234, U249, U264, U279, U294, U309, U324, U339, U354, U369: HDC2010/DSBGA-6; BGA6C100X50P2X3_HDC2010YPAR
U12, U25, U40, U55, U70, U85, U100, U115, U130, U145, U160, U175, U190, U205, U220, U235, U250, U265, U280, U295, U310, U325, U340, U355, U370: MMC5633NJL/WLP-4; WLP-4_0.86x0.86mm_P0.4mm
U13, U26, U41, U56, U71, U86, U101, U116, U131, U146, U161, U176, U191, U206, U221, U236, U251, U266, U281, U296, U311, U326, U341, U356, U371: BH1750FVI-TR; XDCR_BH1750FVI-TR
U14, U27, U42, U57, U72, U87, U102, U117, U132, U147, U162, U177, U192, U207, U222, U237, U252, U267, U282, U297, U312, U327, U342, U357, U372: T117W; DFN-6L
U15, U28, U43, U58, U73, U88, U103, U118, U133, U148, U163, U178, U193, U208, U223, U238, U253, U268, U283, U298, U313, U328, U343, U358, U373: DS1307Z+; SOIC-8_3.9x4.9mm_P1.27mm
U16, U29, U44, U59, U74, U89, U104, U119, U134, U149, U164, U179, U194, U209, U224, U239, U254, U269, U284, U299, U314, U329, U344, U359, U374: ENS210; AMS_QFN-4-1EP_2x2mm_P0.95mm_EP0.7x1.6mm
U19, U30, U45, U60, U75, U90, U105, U120, U135, U150, U165, U180, U195, U210, U225, U240, U255, U270, U285, U300, U315, U330, U345, U360, U375: MTS4; DFN-4L

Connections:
+3.3V: C4.1, C5.1, C7.1, C8.1, C10.1, C11.1, C13.1, C14.1, C16.1, C17.1, C19.1, C20.1, C22.1, C23.1, C25.1, C26.1, C28.1, C29.1, C31.1, C32.1, C34.1, C35.1, C37.1, C38.1, C40.1, C41.1, C43.1, C44.1, C46.1, C47.1, C49.1, C50.1, C52.1, C53.1, C55.1, C56.1, C58.1, C59.1, C61.1, C62.1, C64.1, C65.1, C67.1, C68.1, C70.1, C71.1, C73.1, C74.1, C76.1, C77.1, IC1.3 (VDD), IC2.3 (VDD), IC3.3 (VDD), IC4.3 (VDD), IC5.3 (VDD), IC6.3 (VDD), IC7.3 (VDD), IC8.3 (VDD), IC9.3 (VDD), IC10.3 (VDD), IC11.3 (VDD), IC12.3 (VDD), IC13.3 (VDD), IC14.3 (VDD), IC15.3 (VDD), IC16.3 (VDD), IC17.3 (VDD), IC18.3 (VDD), IC19.3 (VDD), IC20.3 (VDD), IC21.3 (VDD), IC22.3 (VDD), IC23.3 (VDD), IC24.3 (VDD), IC25.3 (VDD), J2.1, J4.1, J6.1, J8.1, J10.1, J12.1, J14.1, J16.1, J18.1, J20.1, J22.1, J24.1, J26.1, J28.1, J30.1, J32.1, J34.1, J36.1, J38.1, J40.1, J42.1, J44.1, J46.1, J48.1, J50.1, R9.1, R10.2, R11.1, R12.1, R13.2, R14.1, R15.1, R16.2, R17.1, R18.1, R19.2, R20.1, R21.1, R22.2, R23.1, R24.1, R25.2, R26.1, R27.1, R28.2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
ADDR: J2.5, J4.5, J6.5, J8.5, J10.5, J12.5, J14.5, J16.5, J18.5, J20.5, J22.5, J24.5, J26.5, J28.5, J30.5, J32.5, J34.5, J36.5, J38.5, J40.5, J42.5, J44.5, J46.5, J48.5, J50.5, U1.4 (ADD0), U2.4 (ADD0), U5.2 (ADDR), U10.2 (ADDR), U11.B1 (ADDR), U13.2 (ADDR), U14.4 (ADDR), U18.2 (ADDR), U23.2 (ADDR), U24.B1 (ADDR), U26.2 (ADDR), U27.4 (ADDR), U31.4 (ADD0), U34.2 (ADDR), U38.2 (ADDR), U39.B1 (ADDR), U41.2 (ADDR), U42.4 (ADDR), U46.4 (ADD0), U49.2 (ADDR), U53.2 (ADDR), U54.B1 (ADDR), U56.2 (ADDR), U57.4 (ADDR), U61.4 (ADD0), U64.2 (ADDR), U68.2 (ADDR), U69.B1 (ADDR), U71.2 (ADDR), U72.4 (ADDR), U76.4 (ADD0), U79.2 (ADDR), U83.2 (ADDR), U84.B1 (ADDR), U86.2 (ADDR), U87.4 (ADDR), U91.4 (ADD0), U94.2 (ADDR), U98.2 (ADDR), U99.B1 (ADDR), U101.2 (ADDR), U102.4 (ADDR), U106.4 (ADD0), U109.2 (ADDR), U113.2 (ADDR), U114.B1 (ADDR), U116.2 (ADDR), U117.4 (ADDR), U121.4 (ADD0), U124.2 (ADDR), U128.2 (ADDR), U129.B1 (ADDR), U131.2 (ADDR), U132.4 (ADDR), U136.4 (ADD0), U139.2 (ADDR), U143.2 (ADDR), U144.B1 (ADDR), U146.2 (ADDR), U147.4 (ADDR), U151.4 (ADD0), U154.2 (ADDR), U158.2 (ADDR), U159.B1 (ADDR), U161.2 (ADDR), U162.4 (ADDR), U166.4 (ADD0), U169.2 (ADDR), U173.2 (ADDR), U174.B1 (ADDR), U176.2 (ADDR), U177.4 (ADDR), U181.4 (ADD0), U184.2 (ADDR), U188.2 (ADDR), U189.B1 (ADDR), U191.2 (ADDR), U192.4 (ADDR), U196.4 (ADD0), U199.2 (ADDR), U203.2 (ADDR), U204.B1 (ADDR), U206.2 (ADDR), U207.4 (ADDR), U211.4 (ADD0), U214.2 (ADDR), U218.2 (ADDR), U219.B1 (ADDR), U221.2 (ADDR), U222.4 (ADDR), U226.4 (ADD0), U229.2 (ADDR), U233.2 (ADDR), U234.B1 (ADDR), U236.2 (ADDR)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
GND: C3.2, C4.2, C5.2, C6.2, C7.2, C8.2, C9.2, C10.2, C11.2, C12.2, C13.2, C14.2, C15.2, C16.2, C17.2, C18.2, C19.2, C20.2, C21.2, C22.2, C23.2, C24.2, C25.2, C26.2, C27.2, C28.2, C29.2, C30.2, C31.2, C32.2, C33.2, C34.2, C35.2, C36.2, C37.2, C38.2, C39.2, C40.2, C41.2, C42.2, C43.2, C44.2, C45.2, C46.2, C47.2, C48.2, C49.2, C50.2, C51.2, C52.2, C53.2, C54.2, C55.2, C56.2, C57.2, C58.2, C59.2, C60.2, C61.2, C62.2, C63.2, C64.2, C65.2, C66.2, C67.2, C68.2, C69.2, C70.2, C71.2, C72.2, C73.2, C74.2, C75.2, C76.2, C77.2, IC1.4 (VSS), IC1.5 (EP), IC2.4 (VSS), IC2.5 (EP), IC3.4 (VSS), IC3.5 (EP), IC4.4 (VSS), IC4.5 (EP), IC5.4 (VSS), IC5.5 (EP), IC6.4 (VSS), IC6.5 (EP), IC7.4 (VSS), IC7.5 (EP), IC8.4 (VSS), IC8.5 (EP), IC9.4 (VSS), IC9.5 (EP), IC10.4 (VSS), IC10.5 (EP), IC11.4 (VSS), IC11.5 (EP), IC12.4 (VSS), IC12.5 (EP), IC13.4 (VSS), IC13.5 (EP), IC14.4 (VSS), IC14.5 (EP), IC15.4 (VSS), IC15.5 (EP), IC16.4 (VSS), IC16.5 (EP), IC17.4 (VSS), IC17.5 (EP), IC18.4 (VSS), IC18.5 (EP), IC19.4 (VSS), IC19.5 (EP), IC20.4 (VSS), IC20.5 (EP), IC21.4 (VSS), IC21.5 (EP), IC22.4 (VSS), IC22.5 (EP), IC23.4 (VSS)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
unnamed: J1.1, J3.1, J5.1, J7.1, J9.1, J11.1, J13.1, J15.1, J17.1, J19.1, J21.1, J23.1, J25.1, J27.1, J29.1, J31.1, J33.1, J35.1, J37.1, J39.1, J41.1, J43.1, J45.1, J47.1, J49.1, U15.1 (X1), U28.1 (X1), U43.1 (X1), U58.1 (X1), U73.1 (X1), U88.1 (X1), U103.1 (X1), U118.1 (X1), U133.1 (X1), U148.1 (X1), U163.1 (X1), U178.1 (X1), U193.1 (X1), U208.1 (X1), U223.1 (X1), U238.1 (X1), U253.1 (X1), U268.1 (X1), U283.1 (X1), U298.1 (X1), U313.1 (X1), U328.1 (X1), U343.1 (X1), U358.1 (X1), U373.1 (X1)
unnamed: J1.2, J3.2, J5.2, J7.2, J9.2, J11.2, J13.2, J15.2, J17.2, J19.2, J21.2, J23.2, J25.2, J27.2, J29.2, J31.2, J33.2, J35.2, J37.2, J39.2, J41.2, J43.2, J45.2, J47.2, J49.2, U15.2 (X2), U28.2 (X2), U43.2 (X2), U58.2 (X2), U73.2 (X2), U88.2 (X2), U103.2 (X2), U118.2 (X2), U133.2 (X2), U148.2 (X2), U163.2 (X2), U178.2 (X2), U193.2 (X2), U208.2 (X2), U223.2 (X2), U238.2 (X2), U253.2 (X2), U268.2 (X2), U283.2 (X2), U298.2 (X2), U313.2 (X2), U328.2 (X2), U343.2 (X2), U358.2 (X2), U373.2 (X2)
unnamed: R1.2, R2.2, R3.2, R4.2, R5.2, R6.2, R7.2, R8.2, R33.2, R37.2, R41.2, R45.2, R49.2, R53.2, R57.2, R61.2, R65.2, R69.2, R73.2, R77.2, R81.2, R85.2, R89.2, R93.2, R97.2, U4.5 (A2), U4.6 (A1), U4.7 (A0), U17.5 (A2), U17.6 (A1), U17.7 (A0), U33.5 (A2), U33.6 (A1), U33.7 (A0), U48.5 (A2), U48.6 (A1), U48.7 (A0), U63.5 (A2), U63.6 (A1), U63.7 (A0), U78.5 (A2), U78.6 (A1), U78.7 (A0), U93.5 (A2), U93.6 (A1), U93.7 (A0), U108.5 (A2), U108.6 (A1), U108.7 (A0), U123.5 (A2), U123.6 (A1), U123.7 (A0), U138.5 (A2), U138.6 (A1), U138.7 (A0), U153.5 (A2), U153.6 (A1), U153.7 (A0), U168.5 (A2), U168.6 (A1), U168.7 (A0), U183.5 (A2), U183.6 (A1), U183.7 (A0), U198.5 (A2), U198.6 (A1), U198.7 (A0), U213.5 (A2), U213.6 (A1), U213.7 (A0), U228.5 (A2), U228.6 (A1), U228.7 (A0), U243.5 (A2), U243.6 (A1), U243.7 (A0), U258.5 (A2), U258.6 (A1), U258.7 (A0), U273.5 (A2), U273.6 (A1), U273.7 (A0), U288.5 (A2), U288.6 (A1), U288.7 (A0), U303.5 (A2), U303.6 (A1), U303.7 (A0), U318.5 (A2), U318.6 (A1), U318.7 (A0), U333.5 (A2), U333.6 (A1), U333.7 (A0), U348.5 (A2), U348.6 (A1), U348.7 (A0), U363.5 (A2), U363.6 (A1), U363.7 (A0)
unnamed: U6.3 (LDR), U6.4 (LED_K), U20.3 (LDR), U20.4 (LED_K), U35.3 (LDR), U35.4 (LED_K), U50.3 (LDR), U50.4 (LED_K), U65.3 (LDR), U65.4 (LED_K), U80.3 (LDR), U80.4 (LED_K), U95.3 (LDR), U95.4 (LED_K), U110.3 (LDR), U110.4 (LED_K), U125.3 (LDR), U125.4 (LED_K), U140.3 (LDR), U140.4 (LED_K), U155.3 (LDR), U155.4 (LED_K), U170.3 (LDR), U170.4 (LED_K), U185.3 (LDR), U185.4 (LED_K), U200.3 (LDR), U200.4 (LED_K), U215.3 (LDR), U215.4 (LED_K), U230.3 (LDR), U230.4 (LED_K), U245.3 (LDR), U245.4 (LED_K), U260.3 (LDR), U260.4 (LED_K), U275.3 (LDR), U275.4 (LED_K), U290.3 (LDR), U290.4 (LED_K), U305.3 (LDR), U305.4 (LED_K), U320.3 (LDR), U320.4 (LED_K), U335.3 (LDR), U335.4 (LED_K), U350.3 (LDR), U350.4 (LED_K), U365.3 (LDR), U365.4 (LED_K)
unnamed: C3.1, C6.1, C9.1, C12.1, C15.1, C18.1, C21.1, C24.1, C27.1, C30.1, C33.1, C36.1, C39.1, C42.1, C45.1, C48.1, C51.1, C54.1, C57.1, C60.1, C63.1, C66.1, C69.1, C72.1, C75.1, R9.2, R12.2, R15.2, R18.2, R21.2, R24.2, R27.2, R30.2, R34.2, R38.2, R42.2, R46.2, R50.2, R54.2, R58.2, R62.2, R66.2, R70.2, R74.2, R78.2, R82.2, R86.2, R90.2, R94.2, R98.2, U13.5 (DVI), U26.5 (DVI), U41.5 (DVI), U56.5 (DVI), U71.5 (DVI), U86.5 (DVI), U101.5 (DVI), U116.5 (DVI), U131.5 (DVI), U146.5 (DVI), U161.5 (DVI), U176.5 (DVI), U191.5 (DVI), U206.5 (DVI), U221.5 (DVI), U236.5 (DVI), U251.5 (DVI), U266.5 (DVI), U281.5 (DVI), U296.5 (DVI), U311.5 (DVI), U326.5 (DVI), U341.5 (DVI), U356.5 (DVI), U371.5 (DVI)
SCL_0: IC1.2 (SCL), IC2.2 (SCL), IC3.2 (SCL), IC4.2 (SCL), IC5.2 (SCL), IC6.2 (SCL), IC7.2 (SCL), IC8.2 (SCL), IC9.2 (SCL), IC10.2 (SCL), IC11.2 (SCL), IC12.2 (SCL), IC13.2 (SCL), IC14.2 (SCL), IC15.2 (SCL), IC16.2 (SCL), IC17.2 (SCL), IC18.2 (SCL), IC19.2 (SCL), IC20.2 (SCL), IC21.2 (SCL), IC22.2 (SCL), IC23.2 (SCL), IC24.2 (SCL), IC25.2 (SCL), J2.4, J4.4, J6.4, J8.4, J10.4, J12.4, J14.4, J16.4, J18.4, J20.4, J22.4, J24.4, J26.4, J28.4, J30.4, J32.4, J34.4, J36.4, J38.4, J40.4, J42.4, J44.4, J46.4, J48.4, J50.4, R10.1, R13.1, R16.1, R19.1, R22.1, R25.1, R28.1, R31.1, R35.1, R39.1, R43.1, R47.1, R51.1, R55.1, R59.1, R63.1, R67.1, R71.1, R75.1, R79.1, R83.1, R87.1, R91.1, R95.1, R99.1, U1.1 (SCL), U2.1 (SCL), U3.6 (SDA/ADDR), U4.1 (SDA), U5.4 (SCL), U6.7 (SCL), U7.A2 (SCL), U8.6 (SDA/ADDR), U9.4 (SCL), U10.4 (SCL), U11.B2 (SCL), U12.A2 (SCL), U13.6 (SCL), U14.1 (SCL), U15.6 (SCL), U16.2 (SCL), U17.1 (SDA), U18.4 (SCL), U19.1 (SCL), U20.7 (SCL), U21.A2 (SCL), U22.4 (SCL), U23.4 (SCL), U24.B2 (SCL), U25.A2 (SCL), U26.6 (SCL), U27.1 (SCL), U28.6 (SCL), U29.2 (SCL), U30.1 (SCL), U31.1 (SCL), U32.6 (SDA/ADDR), U33.1 (SDA), U34.4 (SCL), U35.7 (SCL), U36.A2 (SCL), U37.4 (SCL), U38.4 (SCL), U39.B2 (SCL), U40.A2 (SCL), U41.6 (SCL), U42.1 (SCL), U43.6 (SCL), U44.2 (SCL), U45.1 (SCL)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
SDA_0: IC1.1 (SDA), IC2.1 (SDA), IC3.1 (SDA), IC4.1 (SDA), IC5.1 (SDA), IC6.1 (SDA), IC7.1 (SDA), IC8.1 (SDA), IC9.1 (SDA), IC10.1 (SDA), IC11.1 (SDA), IC12.1 (SDA), IC13.1 (SDA), IC14.1 (SDA), IC15.1 (SDA), IC16.1 (SDA), IC17.1 (SDA), IC18.1 (SDA), IC19.1 (SDA), IC20.1 (SDA), IC21.1 (SDA), IC22.1 (SDA), IC23.1 (SDA), IC24.1 (SDA), IC25.1 (SDA), J2.3, J4.3, J6.3, J8.3, J10.3, J12.3, J14.3, J16.3, J18.3, J20.3, J22.3, J24.3, J26.3, J28.3, J30.3, J32.3, J34.3, J36.3, J38.3, J40.3, J42.3, J44.3, J46.3, J48.3, J50.3, R11.2, R14.2, R17.2, R20.2, R23.2, R26.2, R29.2, R32.2, R36.2, R40.2, R44.2, R48.2, R52.2, R56.2, R60.2, R64.2, R68.2, R72.2, R76.2, R80.2, R84.2, R88.2, R92.2, R96.2, R100.2, U1.6 (SDA), U2.6 (SDA), U3.1 (SCL/INT), U4.2 (SCL), U5.1 (SDA), U6.1 (SDA), U7.B2 (SDA), U8.1 (SCL/INT), U9.6 (SDA), U10.6 (SDA), U11.A2 (SDA), U12.B2 (SDA), U13.4 (SDA), U14.6 (SDA), U15.5 (SDA), U16.3 (SDA), U17.2 (SCL), U18.1 (SDA), U19.4 (SDA), U20.1 (SDA), U21.B2 (SDA), U22.6 (SDA), U23.6 (SDA), U24.A2 (SDA), U25.B2 (SDA), U26.4 (SDA), U27.6 (SDA), U28.5 (SDA), U29.3 (SDA), U30.4 (SDA), U31.6 (SDA), U32.1 (SCL/INT), U33.2 (SCL), U34.1 (SDA), U35.1 (SDA), U36.B2 (SDA), U37.6 (SDA), U38.6 (SDA), U39.A2 (SDA), U40.B2 (SDA), U41.4 (SDA), U42.6 (SDA), U43.5 (SDA), U44.3 (SDA), U45.4 (SDA)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
